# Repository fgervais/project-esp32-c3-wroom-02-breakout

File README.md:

# ESP32-C3-WROOM-02-N4 Breakout Board

## Objective

Make a low cost ESP32-C3 board that can run efficiently from 3x AA lithium
batteries.

## Power Consumption

### Deep Sleep (WROOM only)

## Price

## PCB

## BOM

### Firmware

https://github.com/fgervais/project-idf-c3-test/tree/master/first_arduino_test

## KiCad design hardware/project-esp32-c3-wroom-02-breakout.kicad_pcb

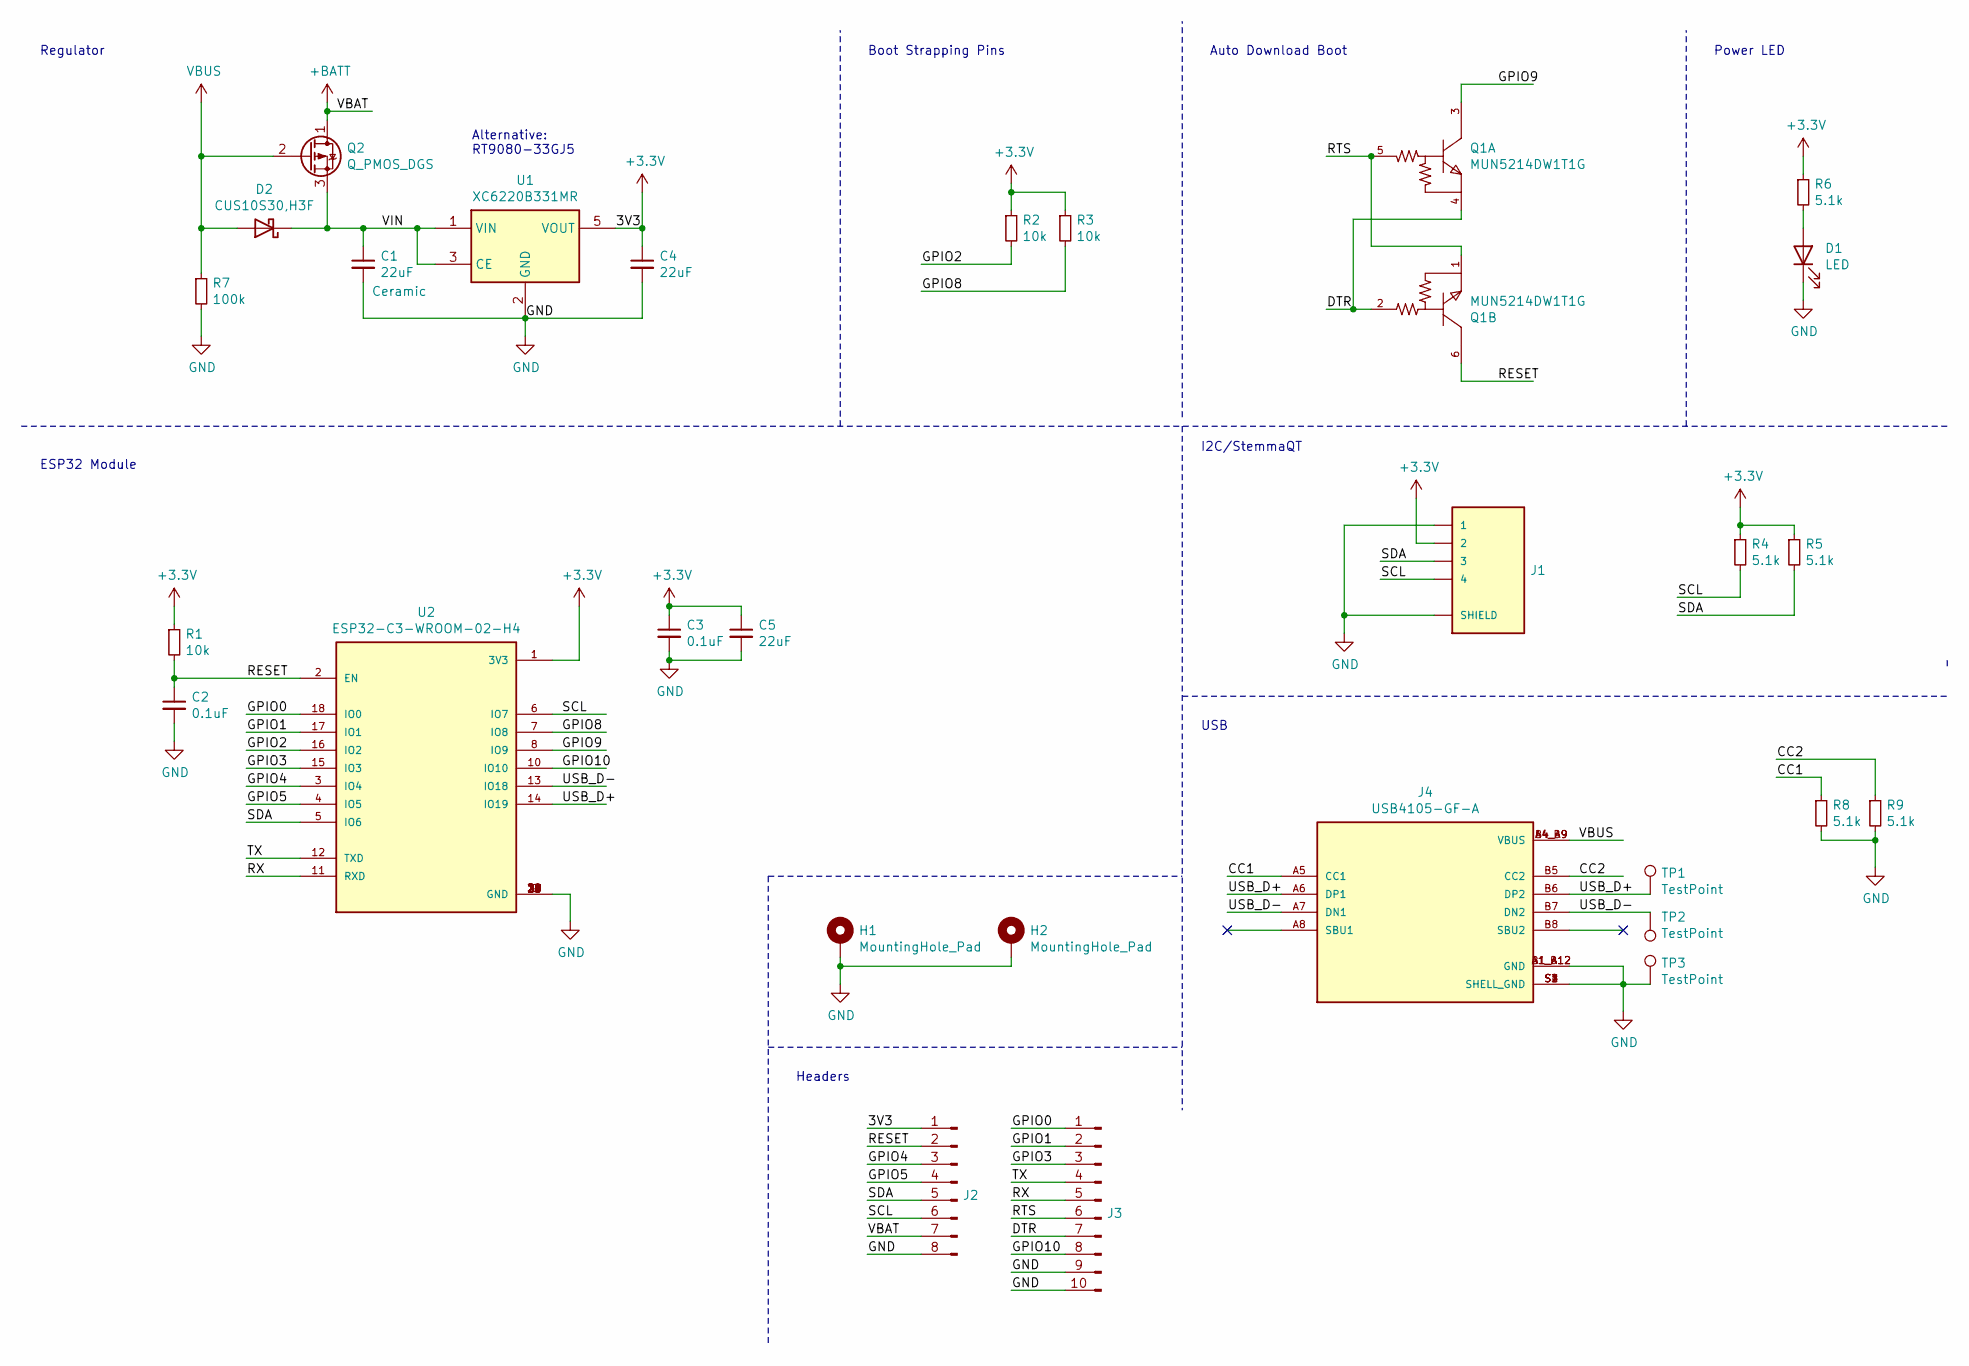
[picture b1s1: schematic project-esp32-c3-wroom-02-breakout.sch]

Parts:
C1, C4, C5: 22uF; C_0805_2012Metric_Pad1.18x1.45mm_HandSolder
C2, C3: 0.1uF; C_0603_1608Metric_Pad1.08x0.95mm_HandSolder
D1: LED; LED_0603_1608Metric
D2: CUS10S30,H3F‎; D_SOD-323
H1, H2: MountingHole_Pad; MountingHole_2.2mm_M2_ISO7380_Pad
J1: SM04B-SRSS-TB(LF)(SN); JST_SM04B-SRSS-TB(LF)(SN)
J2: Conn_01x08_Male; PinHeader_1x08_P2.54mm_Vertical
J3: Conn_01x10_Male; PinHeader_1x10_P2.54mm_Vertical
J4: USB4105-GF-A; GCT_USB4105-GF-A; PARTREV A3
Q1: MUN5214DW1T1G; On_Semiconductor-MUN5214DW1T1G-Manufacturer_Recommended
Q2: Q_PMOS_DGS; SOT50P160X60-6N
R1, R2, R3: 10k; R_0603_1608Metric_Pad0.98x0.95mm_HandSolder
R4, R5, R6, R8, R9: 5.1k; R_0603_1608Metric_Pad0.98x0.95mm_HandSolder
R7: 100k; R_0603_1608Metric_Pad0.98x0.95mm_HandSolder
TP1, TP2, TP3: TestPoint; TestPoint_Pad_D1.0mm
U1: XC6220B331MR; SOT-23-5
U2: ESP32-C3-WROOM-02-H4; MODULE_ESP32-C3-WROOM-02-H4; PARTREV V1.0

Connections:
+3V3: C3.1, C4.1, C5.1, J1.2, J2.1, R1.1, R2.1, R3.1, R4.1, R5.1, R6.1, U1.5 (VOUT), U2.1 (3V3)
+BATT: J2.7, Q2.1 (D)
/CC1: J4.A5 (CC1), R8.1
/CC2: J4.B5 (CC2), R9.1
/DTR: J3.7, Q1.2 (B), Q1.4 (E)
/GPIO0: J3.1, U2.18 (IO0)
/GPIO1: J3.2, U2.17 (IO1)
/GPIO2: R2.2, U2.16 (IO2)
/GPIO3: J3.3, U2.15 (IO3)
/GPIO4: J2.3, U2.3 (IO4)
/GPIO5: J2.4, U2.4 (IO5)
/GPIO8: R3.2, U2.7 (IO8)
/GPIO9: Q1.3 (C), U2.8 (IO9)
/GPIO10: J3.8, U2.10 (IO10)
/RESET: C2.1, J2.2, Q1.6 (C), R1.2, U2.2 (EN)
/RTS: J3.6, Q1.1 (E), Q1.5 (B)
/RX: J3.5, U2.11 (RXD)
/SCL: J1.4, J2.6, R4.2, U2.6 (IO7)
/SDA: J1.3, J2.5, R5.2, U2.5 (IO6)
/TX: J3.4, U2.12 (TXD)
/USB_D+: J4.A6 (DP1), J4.B6 (DP2), TP1.1, U2.14 (IO19)
/USB_D-: J4.A7 (DN1), J4.B7 (DN2), TP2.1, U2.13 (IO18)
/VIN: C1.1, D2.1 (K), Q2.3 (S), U1.1 (VIN), U1.3 (CE)
GND: C1.2, C2.2, C3.2, C4.2, C5.2, D1.1 (K), H1.1, H2.1, J1.1, J1.S1 (SHIELD), J1.S2 (SHIELD), J2.8, J3.9, J3.10, J4.A1_B12 (GND), J4.B1_A12 (GND), J4.S1 (SHELL_GND), J4.S2 (SHELL_GND), J4.S3 (SHELL_GND), J4.S4 (SHELL_GND), R7.2, R8.2, R9.2, TP3.1, U1.2 (GND), U2.9 (GND), U2.19 (GND), U2.20 (GND), U2.21 (GND), U2.22 (GND), U2.23 (GND), U2.24 (GND), U2.25 (GND), U2.26 (GND), U2.27 (GND), U2.28 (GND), U2.29 (GND), U2.30 (GND), U2.31 (GND), U2.32 (GND), U2.33 (GND), U2.34 (GND), U2.35 (GND), U2.36 (GND), U2.37 (GND), U2.38 (GND), U2.39 (GND)
unnamed: D1.2 (A), R6.2
VBUS: D2.2 (A), J4.A4_B9 (VBUS), J4.B4_A9 (VBUS), Q2.2 (G), R7.1

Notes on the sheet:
Regulator
Boot Strapping Pins
Auto Download Boot
Headers
ESP32 Module
I2C/StemmaQT
Power LED
USB
Alternative: ‎RT9080-33GJ5‎

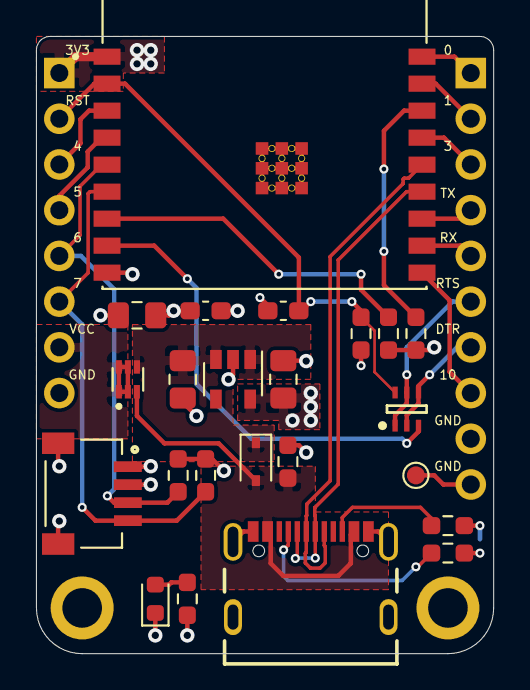
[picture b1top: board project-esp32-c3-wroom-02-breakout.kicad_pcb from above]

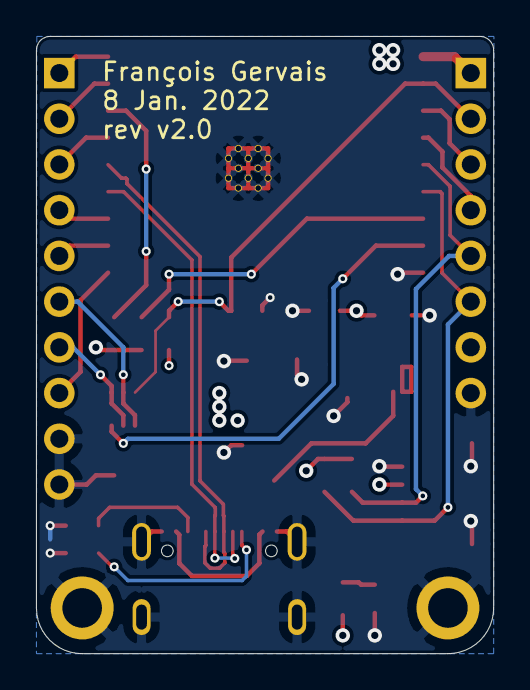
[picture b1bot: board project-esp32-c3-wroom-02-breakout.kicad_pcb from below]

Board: 4 copper layers, 25.4 x 34.3 mm, 27 parts (2 on the bottom side), 26 nets.

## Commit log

2021-09-17 Use wrover breakout project as base
2021-09-24 Schematic ready
2021-09-25 First placement done
2021-09-25 Routing done
2021-10-02 Fix reg cap values in schematic
2021-10-16 Add assembly document
2021-10-17 Change visible layers
2022-01-02 Fix inverted RX/TX labels
2022-01-06 Add p-mosfet, schottky and usb connector to project
2022-01-06 Add USB port to schematic
2022-01-08 Annotate schematic
2022-01-08 Change schottky footprint
2022-01-08 Change mounting hole to M2
2022-01-08 Change schottky footprint for non handsolder
2022-01-08 Power + USB route
2022-01-09 Add version of previous commit
2022-01-18 Link to deep sleep video
2022-01-18 Export schematic
